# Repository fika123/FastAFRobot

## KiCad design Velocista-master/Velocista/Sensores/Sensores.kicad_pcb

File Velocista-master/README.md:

# Velocista
A running robot designed on KiCad

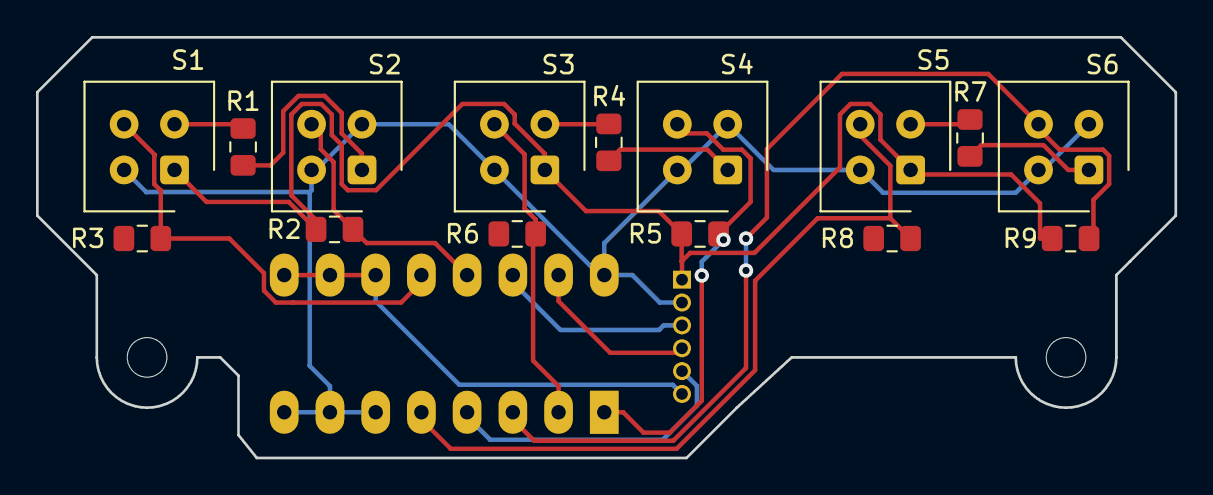
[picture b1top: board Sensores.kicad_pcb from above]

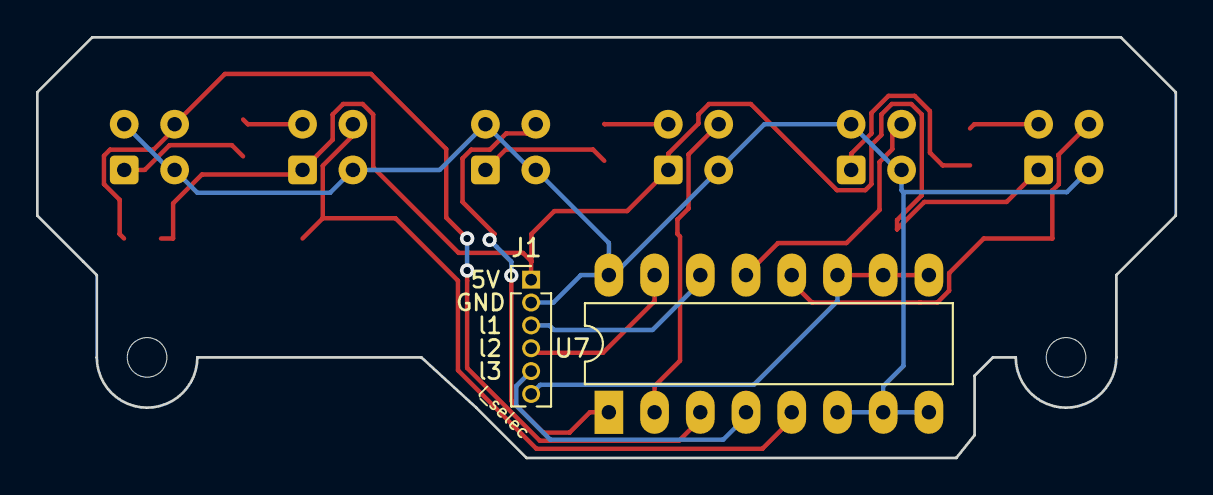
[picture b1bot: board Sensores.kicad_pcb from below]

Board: 2 copper layers, 63.2 x 23.4 mm, 17 parts (2 on the bottom side), 18 nets.

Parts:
J1: Conn_01x06_Female; PinHeader_1x06_P1.27mm_Vertical
R1, R4, R7: 82; R_0805_2012Metric_Pad1.15x1.40mm_HandSolder
R2, R3, R5, R6, R8, R9: 10k; R_0805_2012Metric_Pad1.15x1.40mm_HandSolder
S1, S2, S3, S4, S5, S6: CNY70; Vishay_CNY70
U7: 4053; DIP-16_W7.62mm_LongPads

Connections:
+5V: J1.1, R2.1, R5.1, R9.1, S1.1, S3.1, S5.1
/linea1: J1.3, U7.14
/linea2: J1.4, U7.15
/linea3: J1.5, U7.4
/linea_selec: J1.6, U7.9, U7.10, U7.11
/sensor1: R3.2, S1.3, U7.12
/sensor2: R2.2, S2.3, U7.13
/sensor3: R6.2, S3.3, U7.2
/sensor4: R5.2, S4.3, U7.1
/sensor5: R8.2, S5.3, U7.5
/sensor6: R9.2, S6.3, U7.3
GND: J1.2, S1.4, S2.2, S2.4, S3.4, S4.2, S4.4, S5.4, S6.2, S6.4, U7.6, U7.7, U7.8, U7.16
unnamed: R1.1, S1.2
unnamed: R1.2, S2.1
unnamed: R4.1, S3.2
unnamed: R4.2, S4.1
unnamed: R7.1, S5.2
unnamed: R7.2, S6.1

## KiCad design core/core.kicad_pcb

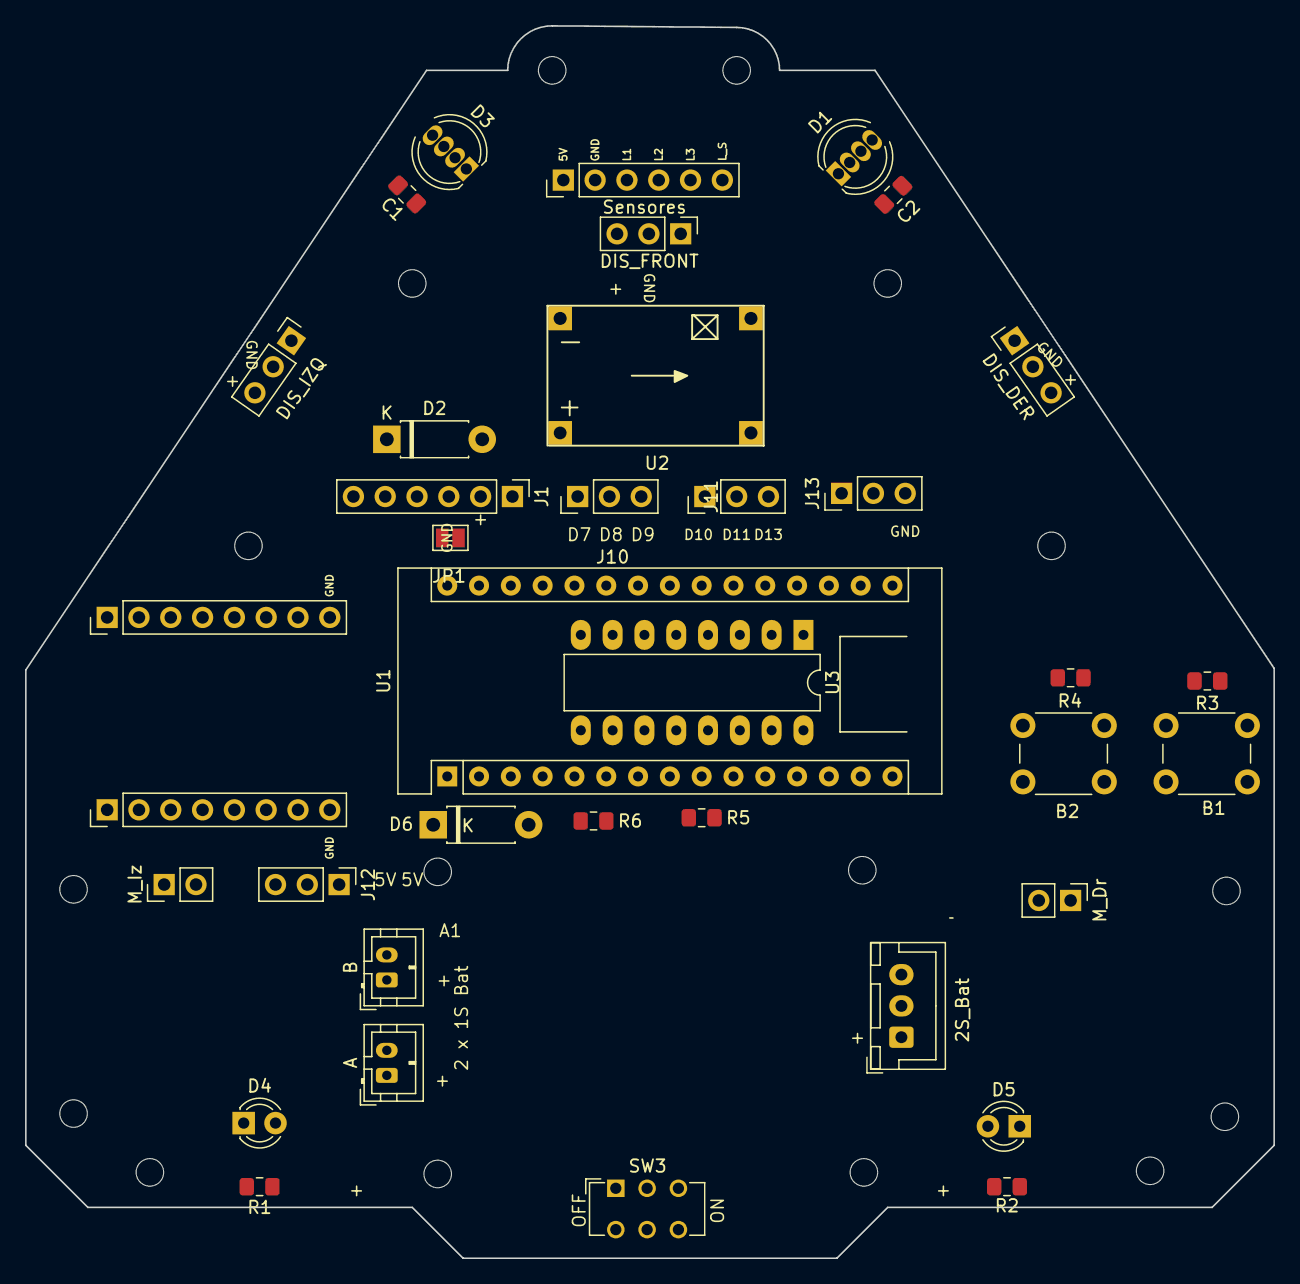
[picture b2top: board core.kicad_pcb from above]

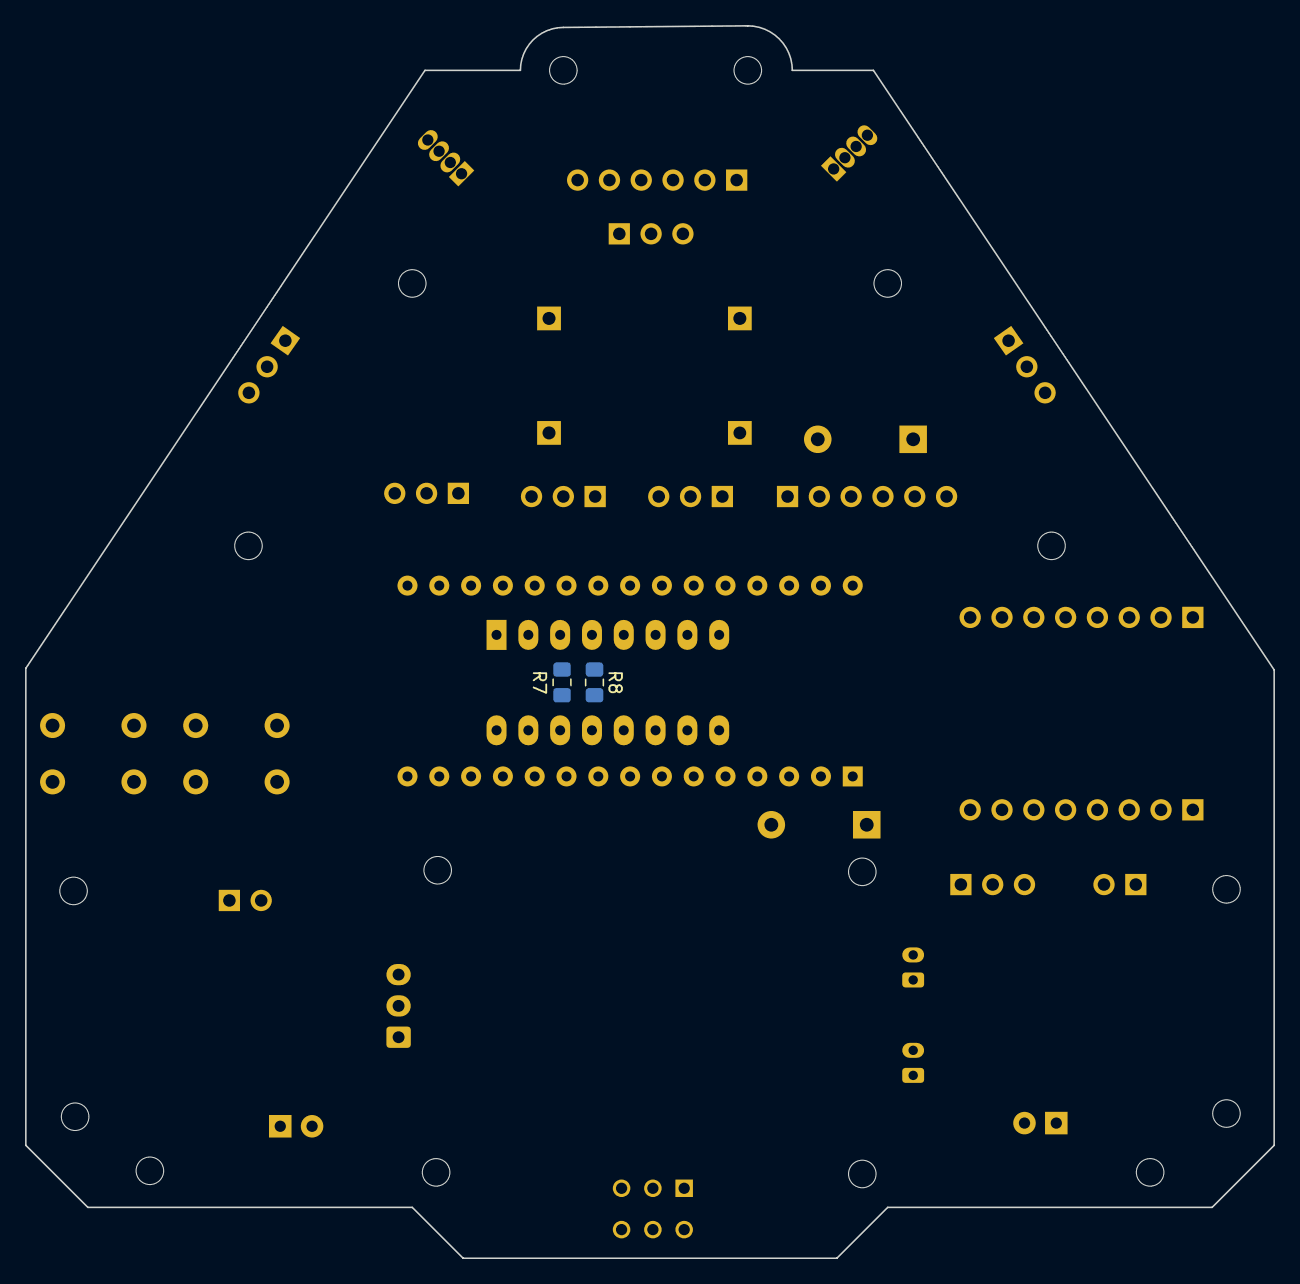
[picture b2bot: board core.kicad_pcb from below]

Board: 2 copper layers, 99.7 x 98.4 mm, 39 parts (2 on the bottom side), 45 nets, no tracks yet.

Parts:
2S_Bat: LIPO_2S; JST_XH_B03B-XH-A_1x03_P2.50mm_Vertical
A: LIPO_1S_A; JST_PH_B2B-PH-K_1x02_P2.00mm_Vertical
B: LIPO_1S_B; JST_PH_B2B-PH-K_1x02_P2.00mm_Vertical
B1: B1; SW_PUSH_6mm
B2: B2; SW_PUSH_6mm
C1, C2: 100nF; C_0805_2012Metric_Pad1.15x1.40mm_HandSolder
D1: NEO1; LED_D5.0mm-4_RGB
D2: 1N4148; D_DO-41_SOD81_P7.62mm_Horizontal
D3: NEO2; LED_D5.0mm-4_RGB
D4: ROJO; LED_D3.0mm
D5: VERDE; LED_D3.0mm
D6: 1N4001; D_DO-41_SOD81_P7.62mm_Horizontal
DIS_DER: DIST_DCHA; PinHeader_1x03_P2.54mm_Vertical
DIS_FRONT: DIST_FRONT; PinHeader_1x03_P2.54mm_Vertical
DIS_IZQ: DIST_IZQ; PinHeader_1x03_P2.54mm_Vertical
J1: HC-05; PinHeader_1x06_P2.54mm_Vertical
J2: TB6612FNG_A; PinHeader_1x08_P2.54mm_Vertical
J5: TB6612FNG_B; PinHeader_1x08_P2.54mm_Vertical
J10: AUX1; PinHeader_1x03_P2.54mm_Vertical
J11: AUX2; PinHeader_1x03_P2.54mm_Vertical
J12: AUX3; PinHeader_1x03_P2.54mm_Vertical
J13: AUX4; PinHeader_1x03_P2.54mm_Vertical
JP1: Jumper; SolderJumper-2_P1.3mm_Open_Pad1.0x1.5mm
M_Dr: MOT_DER; PinHeader_1x02_P2.54mm_Vertical
M_Iz: MOT_IZQ; PinHeader_1x02_P2.54mm_Vertical
R1, R2: 220; R_0805_2012Metric_Pad1.15x1.40mm_HandSolder
R3, R4: 10K; R_0805_2012Metric_Pad1.15x1.40mm_HandSolder
R5: 82K; R_0805_2012Metric_Pad1.15x1.40mm_HandSolder
R6: 120K; R_0805_2012Metric_Pad1.15x1.40mm_HandSolder
R7, R8: 1k; R_0805_2012Metric_Pad1.15x1.40mm_HandSolder
SW3: SW_DPDT_x2; SW_CuK_JS202011CQN_DPDT_Straight
Sensores: Sensores_linea; PinHeader_1x06_P2.54mm_Vertical
U1: Arduino_Nano_v3.x; Arduino_Nano
U2: DC-DC_BuckModule; DC-DC-MP2307
U3: PCF8574; DIP-16_W7.62mm_LongPads

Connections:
+5V: C1.2, C2.2, D1.3, D3.3, D6.1, DIS_DER.3, DIS_FRONT.3, DIS_IZQ.3, J1.2, J2.2, J12.2, J12.3, R1.1, R2.1, R3.1, R4.1, R7.1, R8.1, SW3.5, Sensores.1, U1.27, U2.3, U3.16
A1: J12.1, U1.20
B1: B1.1, R3.2, U3.11
B2: B2.1, R4.2, U3.12
BAT: D6.2, R5.2, R6.1, U1.19
BT_RX: J1.5, U1.1
BT_TX: D2.2, U1.2
D7: J10.1, U1.10
D8: J10.2, U1.11
D9: J10.3, U1.12
D10: J11.1, U1.13
D11: J11.2, U1.14
D13: J11.3, U1.16
DIR_DER_1: J5.5, U3.9
DIR_DER_2: J5.6, U3.10
DIR_IZQ_1: J5.3, U3.6
DIR_IZQ_2: J5.2, U3.7
DIST_DCHA: DIS_DER.1, U1.24
DIST_FRONT: DIS_FRONT.1, U1.25
DIST_IZQ: DIS_IZQ.1, U1.26
GND: 2S_Bat.3, B.2, B1.2, B2.2, C1.1, C2.1, D1.2, D3.2, DIS_DER.2, DIS_FRONT.2, DIS_IZQ.2, J1.3, J2.3, J2.8, J5.8, J13.1, J13.2, J13.3, R6.2, Sensores.2, U1.4, U1.29, U2.2, U2.4, U3.1, U3.2, U3.3, U3.8
I2C_SCL: R8.2, U1.8, U3.14
I2C_SDA: R7.2, U1.7, U3.15
LED_G: D5.1, U3.4
LED_R: D4.1, U3.5
LINEA_1: Sensores.3, U1.21
LINEA_2: Sensores.4, U1.22
LINEA_3: Sensores.5, U1.23
LINEA_SEL: Sensores.6, U1.15
M_DER_+: J2.7, M_Dr.2
M_DER_-: J2.6, M_Dr.1
M_IZQ_+: J2.4, M_Iz.2
M_IZQ_-: J2.5, M_Iz.1
NEO: D1.4, U1.5
unnamed: D1.1, D3.4
unnamed: D2.1, J1.4
unnamed: D4.2, R1.2
unnamed: D5.2, R2.2
unnamed: A.2, B.1
PWM_DER: J5.7, U1.6
PWM_IZQ: J5.1, U1.9
STBY_MOT: J5.4, SW3.6
VBAT: 2S_Bat.1, A.1, J2.1, SW3.2
VCC: JP1.2, U1.30
VDD: JP1.1, R5.1, SW3.3, U2.1

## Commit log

2018-11-17 Add files via upload
    Sensores Xd
2018-12-01 Add files via upload
    Sensors finished
2018-12-01 Add files via upload
    Placa final
